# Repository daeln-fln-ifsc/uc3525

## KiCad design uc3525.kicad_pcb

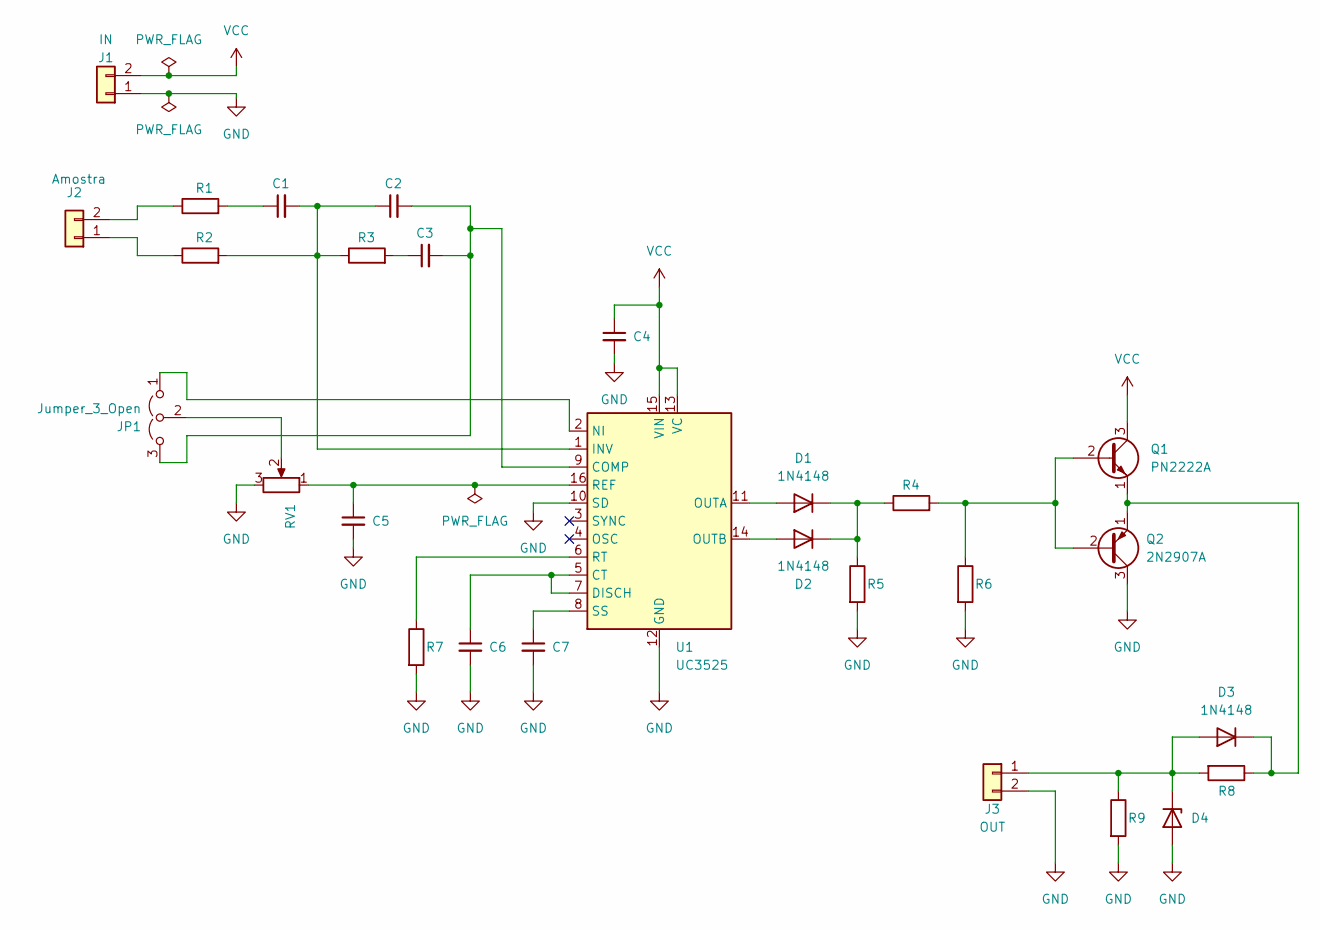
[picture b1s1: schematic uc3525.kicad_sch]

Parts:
C1, C2, C3, C4, C5, C6, C7: C_Small; C_Disc_D6.0mm_W2.5mm_P5.00mm_HandSolder
D1, D2, D3: 1N4148; D_DO-35_SOD27_P10.16mm_Horizontal_HandSolder
D4: D_Zener; D_DO-41_SOD81_P10.16mm_Horizontal_HandSolder
J1: IN; TerminalBlock_Phoenix_MKDS-1,5-2_1x02_P5.00mm_Horizontal
J2: Amostra; TerminalBlock_Phoenix_MKDS-1,5-2_1x02_P5.00mm_Horizontal
J3: OUT; TerminalBlock_Phoenix_MKDS-1,5-2_1x02_P5.00mm_Horizontal
JP1: Jumper_3_Open; PinHeader_1x03_P2.54mm_Vertical_HandSolder
Q1: PN2222A; TO-92_Inline_Wide_HandSolder
Q2: 2N2907A; TO-18-3_HandSolder
R1, R2, R3, R4, R5, R6, R7, R8, R9: R; R_Axial_DIN0207_L6.3mm_D2.5mm_P10.16mm_Horizontal_HandSolder
RV1: R_Potentiometer; Potentiometer_Bourns_3296X_Horizontal_HandSolder
U1: UC3525; DIP-16_W7.62mm_Socket_LongPads

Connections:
GND: C4.2, C5.2, C6.2, C7.2, D4.2 (A), J1.1, J3.2, Q2.3 (C), R5.2, R6.2, R7.2, R9.2, RV1.3, U1.10 (SD), U1.12 (GND)
unnamed: C1.1, R1.2
unnamed: C3.1, R3.2
unnamed: D1.2 (A), U1.11 (OUTA)
unnamed: D1.1 (K), D2.1 (K), R4.1, R5.1
unnamed: D2.2 (A), U1.14 (OUTB)
unnamed: D3.2 (A), D4.1 (K), J3.1, R8.2, R9.1
unnamed: D3.1 (K), Q1.1 (E), Q2.1 (E), R8.1
unnamed: J2.1, R2.1
unnamed: J2.2, R1.1
unnamed: JP1.1 (A), U1.2 (NI)
unnamed: C2.2, C3.2, JP1.3 (B), U1.9 (COMP)
unnamed: JP1.2 (C), RV1.2
unnamed: Q1.2 (B), Q2.2 (B), R4.2, R6.1
unnamed: C6.1, U1.5 (CT), U1.7 (DISCH)
unnamed: C1.2, C2.1, R2.2, R3.1, U1.1 (INV)
unnamed: C5.1, RV1.1, U1.16 (REF)
unnamed: R7.1, U1.6 (RT)
unnamed: C7.1, U1.8 (SS)
VCC: C4.1, J1.2, Q1.3 (C), U1.13 (VC), U1.15 (VIN)

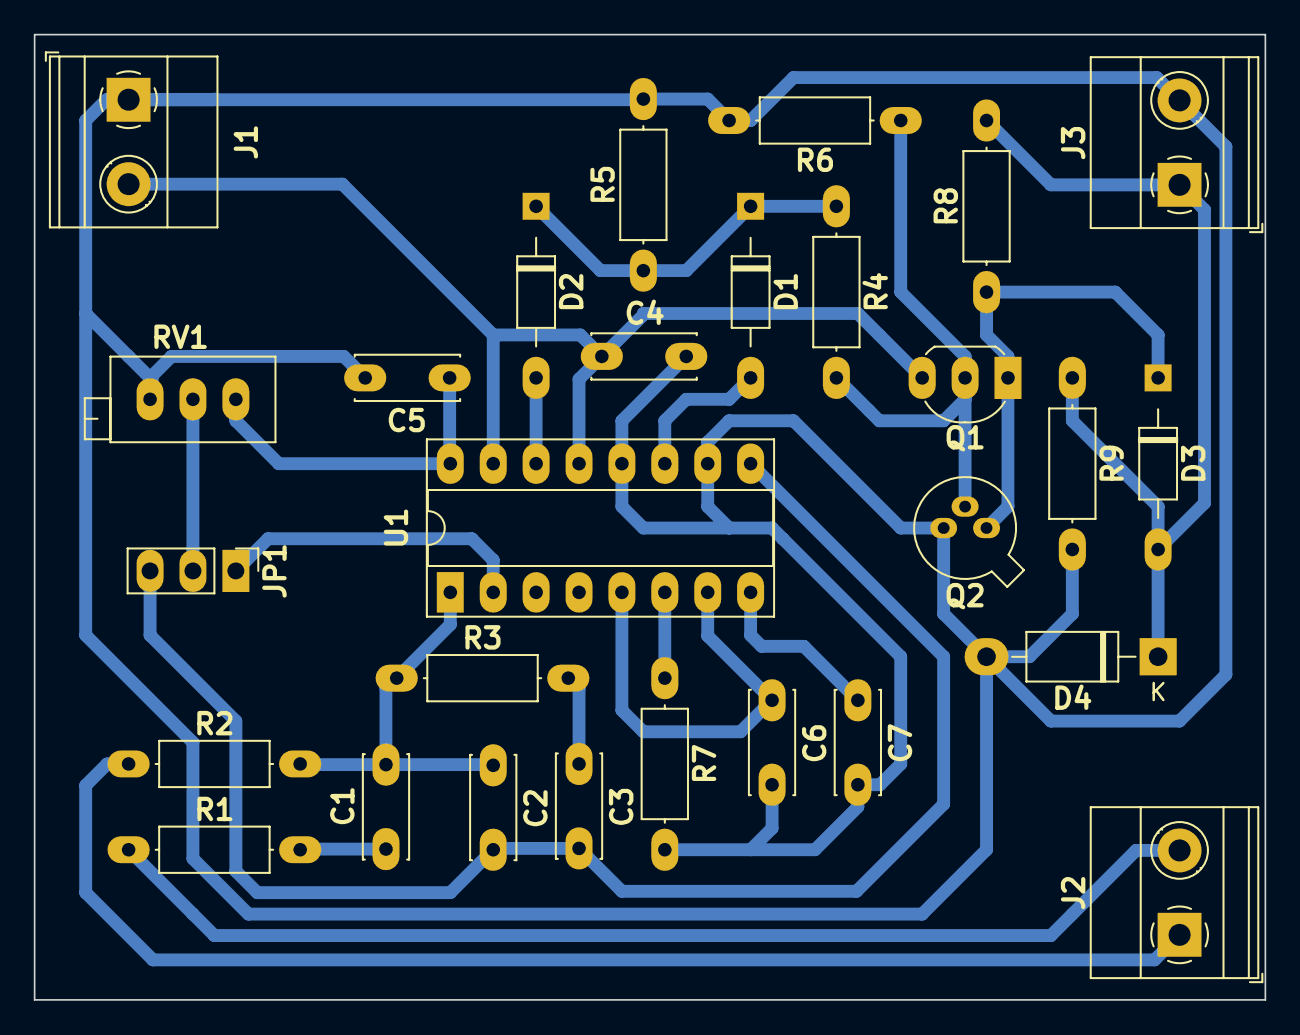
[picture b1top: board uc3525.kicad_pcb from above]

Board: 2 copper layers, 72.9 x 57.2 mm, 28 parts (0 on the bottom side), 20 nets.

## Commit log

2023-08-30 Primeiro commit.
2023-08-30 Aumento do clearance.
2023-08-30 Aumento no tamanho dos textos dos componentes footprint.
2023-09-04 Aumento da distância entre as trilhas.
2023-10-02 Adicionados arquivos pdf do esquemático e do layout.
